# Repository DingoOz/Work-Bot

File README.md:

# Work-Bot
2022 Semester 2

//TODO
* document code more
* factor the code to use functions more
* document a possible Finite State Machine that calls these functions
* implement a watchdog timer to detect if robot is not making progress

== Diagnostic Routine ==
Possibly create a separate program to act as a diagnostic program to test all functions of the hardward.

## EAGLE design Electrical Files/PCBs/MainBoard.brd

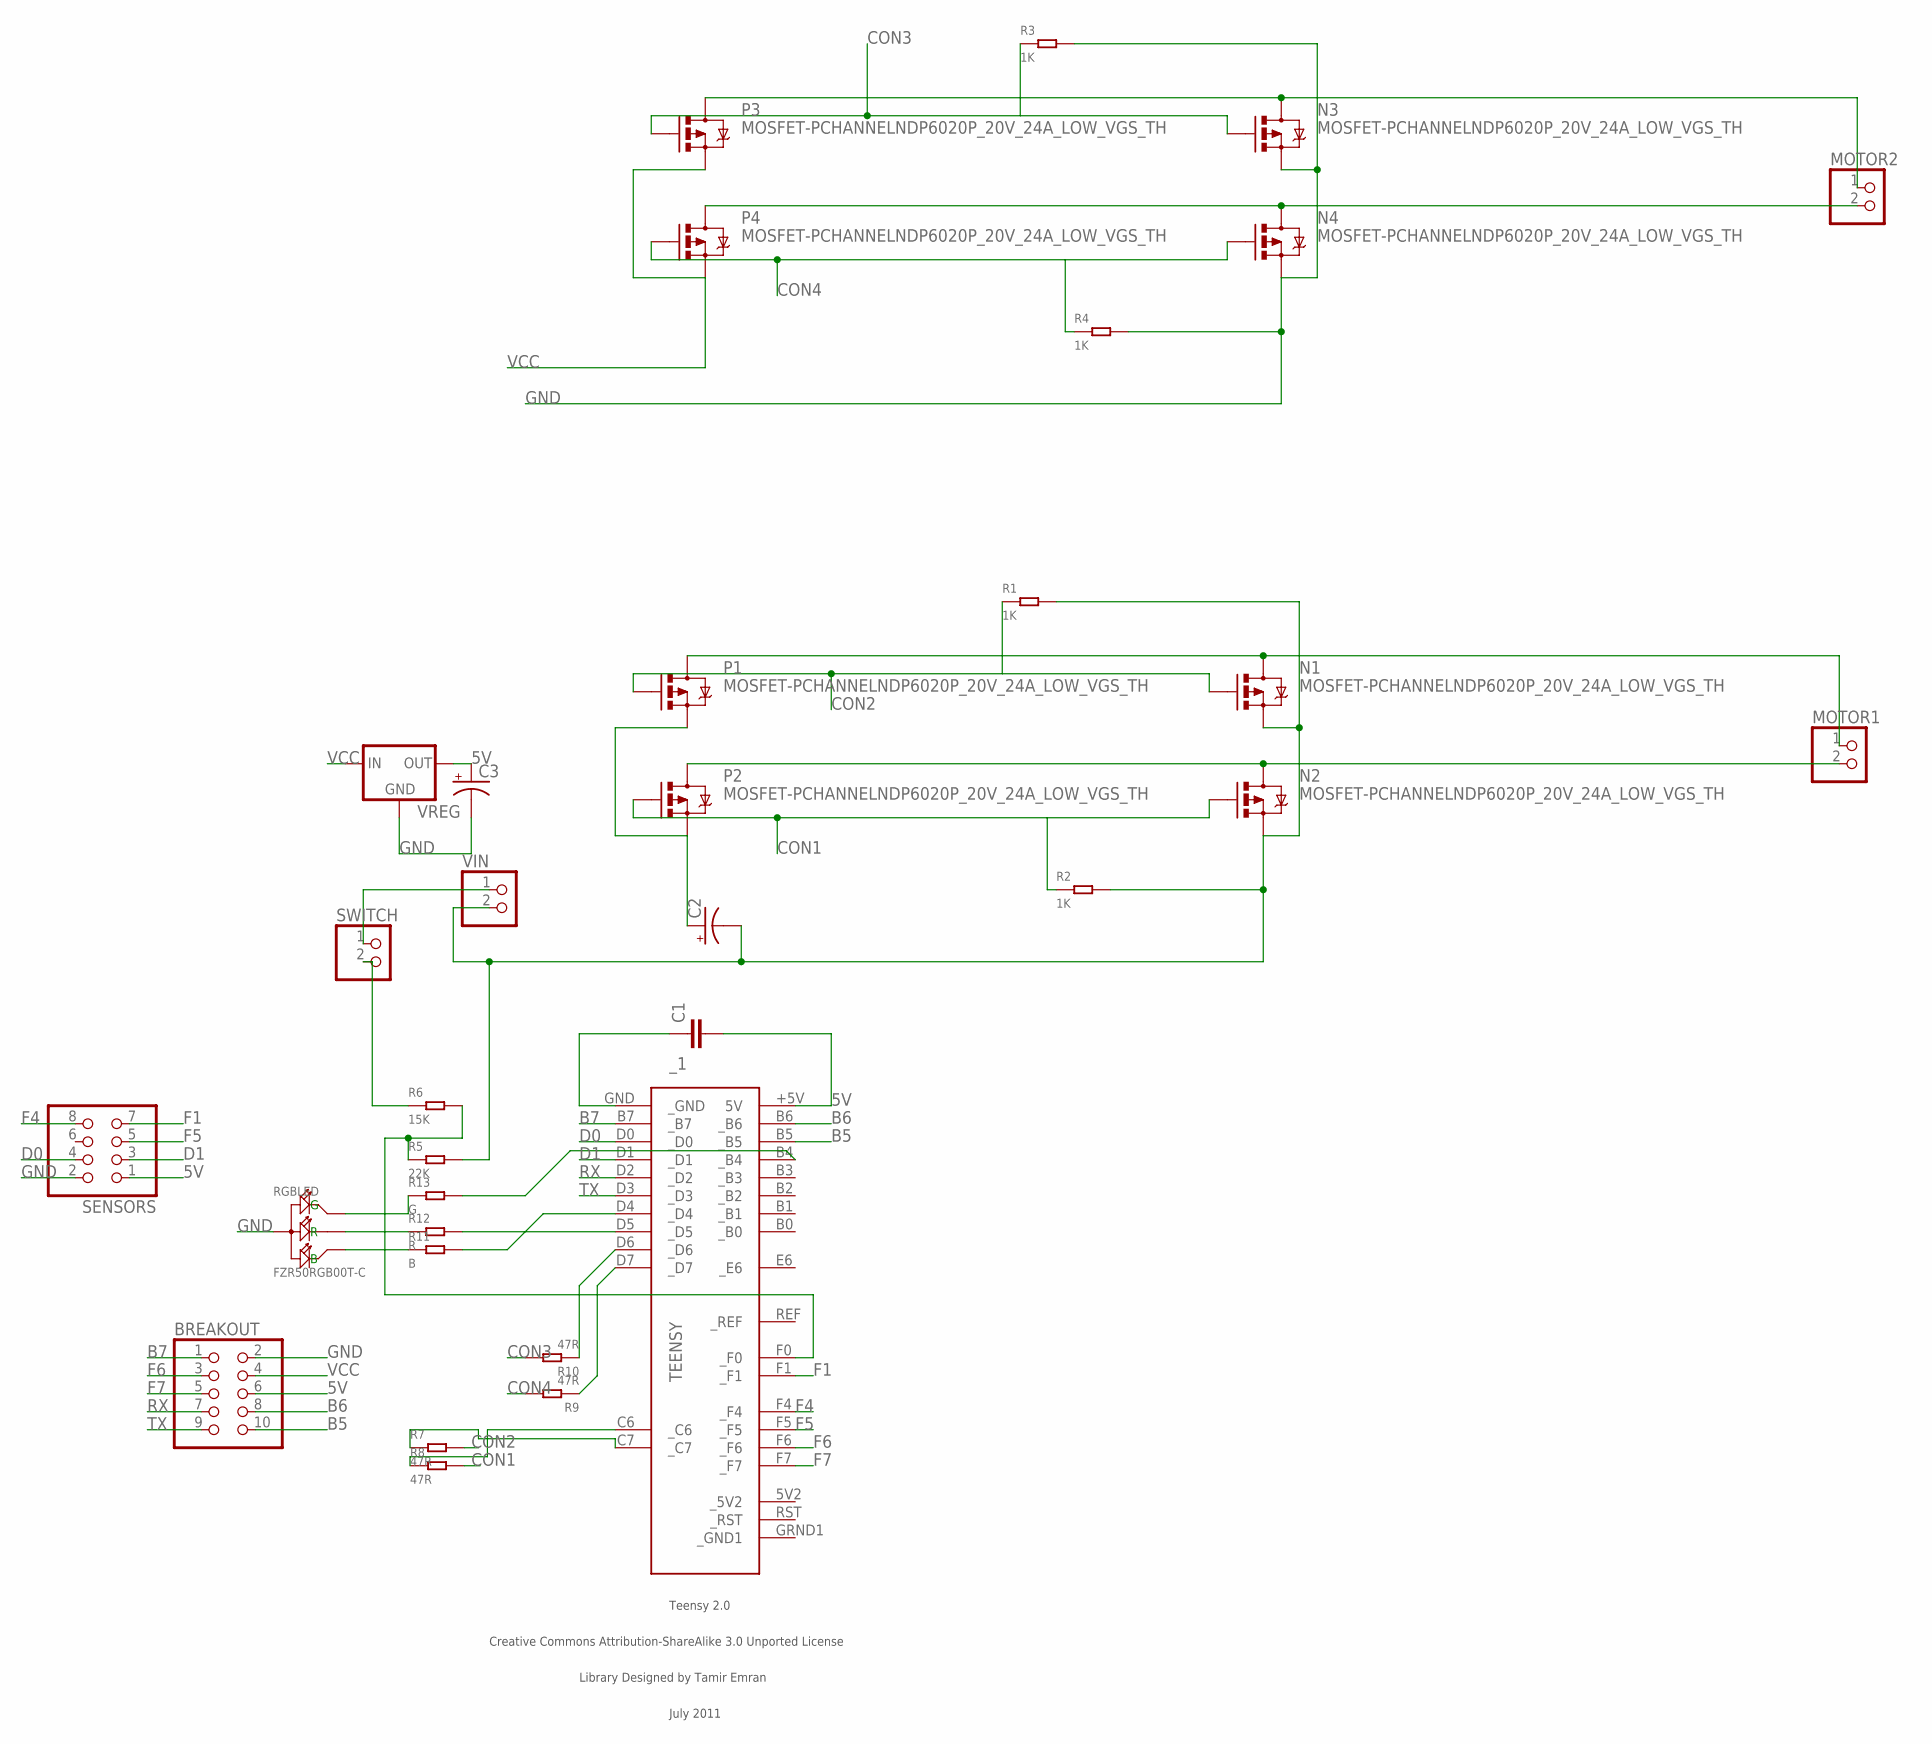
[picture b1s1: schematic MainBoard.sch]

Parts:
BREAKOUT: PINHD-2X5; 2X05
C1: CAPPTH; CAP-PTH-SMALL
C2, C3: CAP_POLPTH2; CPOL-RADIAL-10UF-25V
MOTOR1, MOTOR2: PINHD-1X2; 1X02
N1, N2, N3, N4: MOSFET-PCHANNELNDP6020P_20V_24A_LOW_VGS_TH; TO220V
P1, P2, P3, P4: MOSFET-PCHANNELNDP6020P_20V_24A_LOW_VGS_TH; TO220V
R1, R2, R3, R4: 1K; PR-D2.3XL6.5MM
R5: 22K; PR-D2.3XL6.5MM
R6: 15K; PR-D2.3XL6.5MM
R7, R8, R9, R10: 47R; PR-D2.3XL6.5MM
R11: B; PR-D2.3XL6.5MM
R12: R; PR-D2.3XL6.5MM
R13: G; PR-D2.3XL6.5MM
RGBLED: FZR50RGB00T-C; LED4-1.3-D5.0MM
SENSORS: PINHD-2X4; 2X04
SWITCH: PINHD-1X2; 1X02
VIN: PINHD-1X2; 1X02
VREG: V_REG_78XXSINK; TO220-IGO
_1: TEENSY

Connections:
5V: BREAKOUT.6, C1.2, C3.1 (+), SENSORS.1, VREG.OUT, _1.+5V (5V)
B5: BREAKOUT.10, _1.B5 (_B5)
B6: BREAKOUT.8, _1.B6 (_B6)
B7: BREAKOUT.1, _1.B7 (_B7)
CON1: N2.1 (G), P2.1 (G), R2.1, R8.2
CON2: N1.1 (G), P1.1 (G), R1.1, R7.2
CON3: N3.1 (G), P3.1 (G), R3.1, R10.2
CON4: N4.1 (G), P4.1 (G), R4.1, R9.2
D0: SENSORS.4, _1.D0 (_D0)
D1: SENSORS.3, _1.D1 (_D1)
F1: SENSORS.7, _1.F1 (_F1)
F4: SENSORS.8, _1.F4 (_F4)
F5: SENSORS.5, _1.F5 (_F5)
F6: BREAKOUT.3, _1.F6 (_F6)
F7: BREAKOUT.5, _1.F7 (_F7)
GND: BREAKOUT.2, C1.1, C2.2 (-), C3.2 (-), N1.3 (S), N2.3 (S), N3.3 (S), N4.3 (S), R1.2, R2.2, R3.2, R4.2, R5.2, RGBLED.C (+), SENSORS.2, VIN.2, VREG.GND, _1.GND (_GND)
unnamed: MOTOR1.1, N1.2 (D), P1.2 (D)
unnamed: R10.1, _1.D6 (_D6)
unnamed: MOTOR1.2, N2.2 (D), P2.2 (D)
unnamed: MOTOR2.2, N4.2 (D), P4.2 (D)
unnamed: R9.1, _1.D7 (_D7)
unnamed: MOTOR2.1, N3.2 (D), P3.2 (D)
unnamed: R7.1, _1.C7 (_C7)
unnamed: R8.1, _1.C6 (_C6)
unnamed: R5.1, R6.2, _1.F0 (_F0)
unnamed: R11.2, _1.D4 (_D4)
unnamed: SWITCH.1, VIN.1
unnamed: R12.2, _1.D5 (_D5)
unnamed: R13.2, _1.B4 (_B4)
unnamed: R13.1, RGBLED.G
unnamed: R12.1, RGBLED.R
unnamed: R11.1, RGBLED.B
RX: BREAKOUT.7, _1.D2 (_D2)
TX: BREAKOUT.9, _1.D3 (_D3)
VCC: BREAKOUT.4, C2.1 (+), P1.3 (S), P2.3 (S), P3.3 (S), P4.3 (S), R6.1, SWITCH.2, VREG.IN

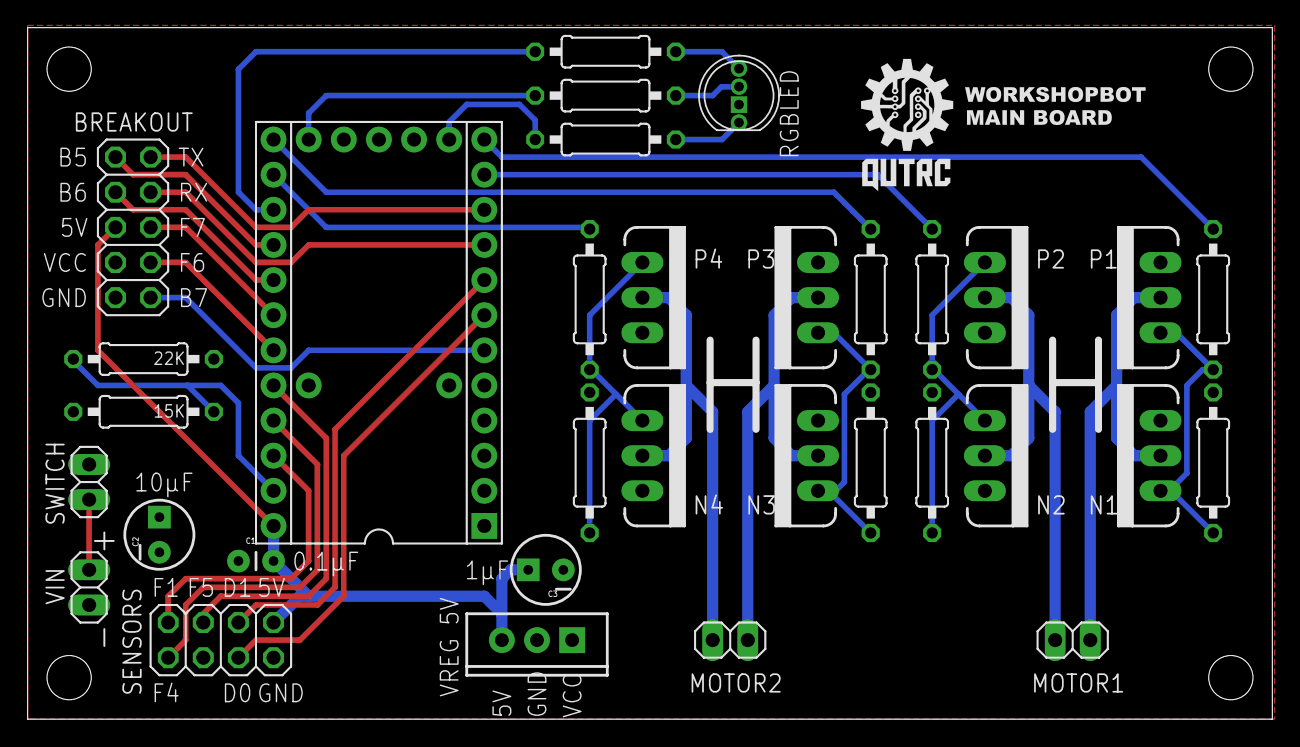
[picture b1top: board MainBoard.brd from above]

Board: 2 copper layers, 90.0 x 50.0 mm, 34 parts (0 on the bottom side), 35 nets.

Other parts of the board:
U$1: LOGO1

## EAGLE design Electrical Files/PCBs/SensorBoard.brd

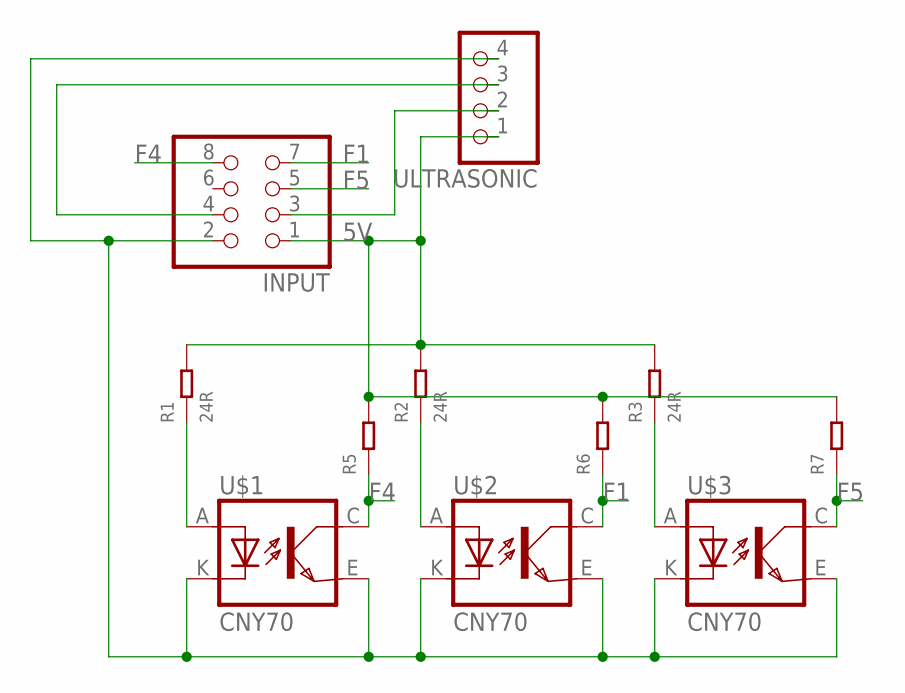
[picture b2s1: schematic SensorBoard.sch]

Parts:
INPUT: PINHD-2X4; 2X04
R1, R2, R3: 24R; PR-D2.3XL6.5MM
R5, R6, R7: DIP-RES-0R-5%-1/4W(2P-D2.3XL6.5MM); PR-D2.3XL6.5MM
U$1, U$2, U$3: CNY70; 4
ULTRASONIC: PINHD-1X4; 1X04

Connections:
5V: INPUT.1, R1.2, R2.2, R3.2, R5.2, R6.2, R7.2, ULTRASONIC.1
F1: INPUT.7, R6.1, U$2.C (COL)
F4: INPUT.8, R5.1, U$1.C (COL)
F5: INPUT.5, R7.1, U$3.C (COL)
GND: INPUT.2, U$1.E (EMI), U$1.K (C), U$2.E (EMI), U$2.K (C), U$3.E (EMI), U$3.K (C), ULTRASONIC.4
unnamed: R2.1, U$2.A
unnamed: INPUT.3, ULTRASONIC.2
unnamed: INPUT.4, ULTRASONIC.3
unnamed: R3.1, U$3.A
unnamed: R1.1, U$1.A

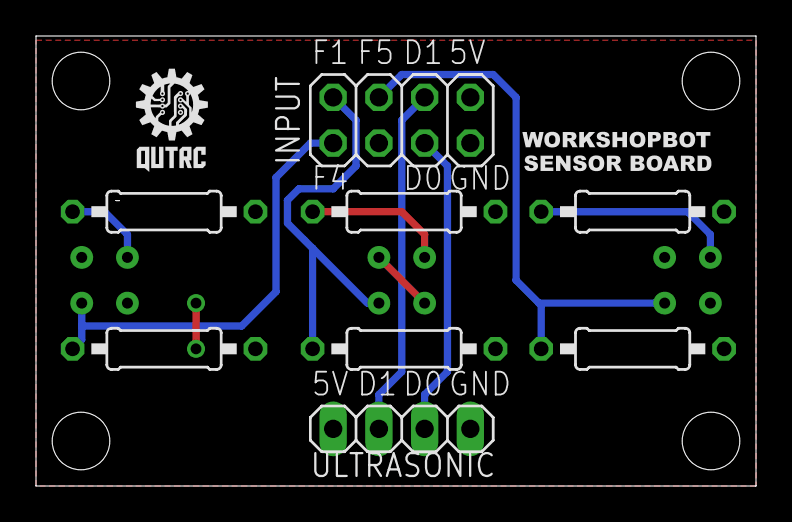
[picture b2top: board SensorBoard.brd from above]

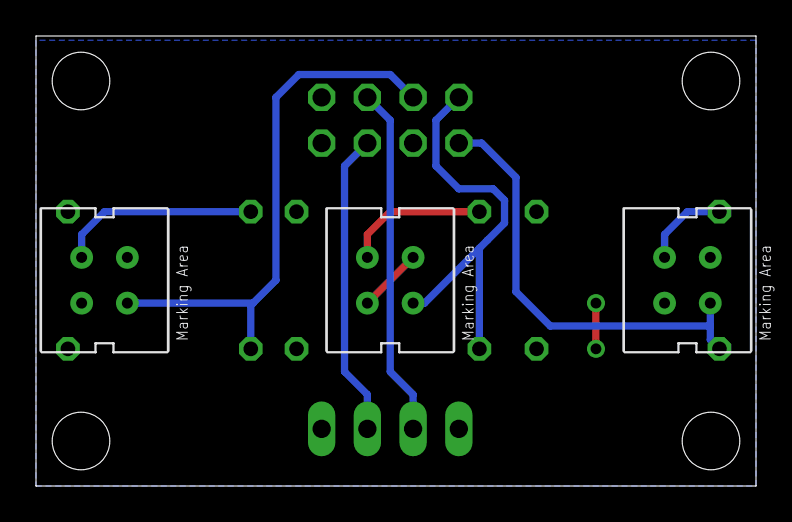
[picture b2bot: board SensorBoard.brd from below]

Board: 2 copper layers, 40.0 x 25.0 mm, 13 parts (3 on the bottom side), 10 nets.

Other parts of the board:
U$4: LOGO21
U$5: LOGO22

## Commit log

2022-03-14 Adding original files and new files
    Creation of github repo for 2017 workshop called workbots. Adding the original files from the google drive alogn with example maze solving and line following code.
2022-07-27 Update mazesolver.ino
    Started to add more comments to the code
2022-07-27 Update mazesolver.ino
    Modified the base code to reflect the code used on Tuesday 27/7/2022
2022-07-28 Update mazesolver.ino
    Added comments re wallahead function
2022-07-28 Added header and battery check
    Added mazesolver.h
    Added the beginnings of a Initial Battery Check routine that stops and blinks RED if battery is low
    Moved some unused code into a Diagnostics routine file (started, not yet finished)
2022-07-28 Update mazesolver.ino
    Added red light blink loop if the battery voltage is measured as too low to run. Red LED blinks 5 times, waits 3 seconds, blinks 5 time...forever.
2022-07-28 Update mazesolver.ino
    Removed unneeded diagnostic comment

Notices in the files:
parts and their libraries:
SparkFun-DiscreteSemi: Licensing: Creative Commons ShareAlike 4.0 International - https://creativecommons.org/licenses/by-sa/4.0
teensy: Creative Commons Attribution-ShareAlike 3.0 Unported License
teensy: Licensed Under Creative Commons Attribution-ShareAlike 3.0 Unported (CC BY-SA 3.0)
